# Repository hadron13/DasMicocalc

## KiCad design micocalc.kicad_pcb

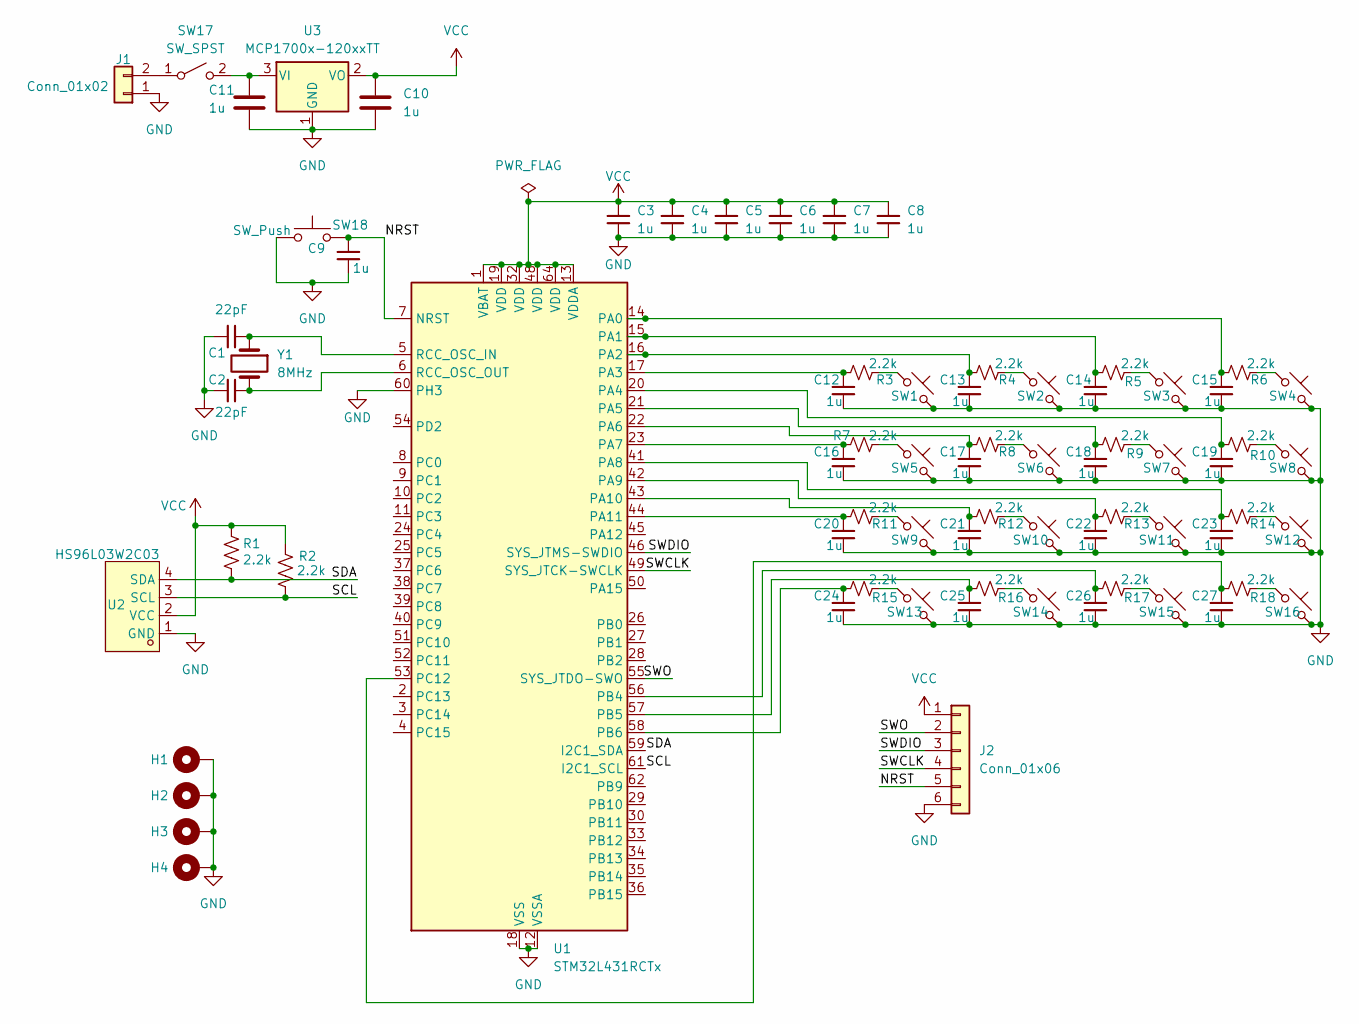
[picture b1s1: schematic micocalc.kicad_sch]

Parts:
C1, C2: 22pF; C_Disc_D3.0mm_W2.0mm_P2.50mm
C3, C4, C5, C6, C7, C8, C9, C10, C11, C12, C13, C14, C15, C16, C17, C18, C19, C20, C21, C22, C23, C24, C25, C26, C27: 1u; C_0603_1608Metric_Pad1.08x0.95mm_HandSolder
H1, H2, H3, H4: MountingHole_Pad; MountingHole_2.2mm_M2_Pad_Via
J1: Conn_01x02; PinHeader_1x02_P2.54mm_Vertical
J2: Conn_01x06; PinSocket_1x06_P2.54mm_Vertical
R1, R2, R3, R4, R5, R6, R7, R8, R9, R10, R11, R12, R13, R14, R15, R16, R17, R18: 2.2k; R_0603_1608Metric_Pad0.98x0.95mm_HandSolder
SW1, SW2, SW3, SW4, SW5, SW6, SW7, SW8, SW9, SW10, SW11, SW12, SW13, SW14, SW15, SW16: SW_Push_45deg; SW_Push_1P1T_NO_E-Switch_TL3301NxxxxxG
SW17: SW_SPST; SW-TH_3P-L8.6-W4.5-P2.60
SW18: SW_Push; SW_Push_1P1T_NO_E-Switch_TL3301NxxxxxG
U1: STM32L431RCTx; LQFP-64_10x10mm_P0.5mm
U2: HS96L03W2C03; OLED-TH_L27.8-W27.2-P2.54_C9900033791; LCSC Part C5248080
U3: MCP1700x-120xxTT; SOT-23
Y1: 8MHz; Crystal_HC49-U_Vertical

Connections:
/NRST: C9.1, J2.5, SW18.2, U1.7 (NRST)
/SCL: R2.2, U1.61 (I2C1_SCL), U2.3 (SCL)
/SDA: R1.2, U1.59 (I2C1_SDA), U2.4 (SDA)
/SWCLK: J2.4, U1.49 (SYS_JTCK-SWCLK)
/SWDIO: J2.3, U1.46 (SYS_JTMS-SWDIO)
/SWO: J2.2, U1.55 (SYS_JTDO-SWO)
GND: C1.1, C2.1, C3.2, C4.2, C5.2, C6.2, C7.2, C8.2, C9.2, C10.2, C11.2, C12.2, C13.2, C14.2, C15.2, C16.2, C17.2, C18.2, C19.2, C20.2, C21.2, C22.2, C23.2, C24.2, C25.2, C26.2, C27.2, H1.1 (1_1), H2.1 (1_1), H3.1 (1_1), H4.1 (1_1), J1.1, J2.6, SW1.2, SW2.2, SW3.2, SW4.2, SW5.2, SW6.2, SW7.2, SW8.2, SW9.2, SW10.2, SW11.2, SW12.2, SW13.2, SW14.2, SW15.2, SW16.2, SW18.1, U1.12 (VSSA), U1.18 (VSS), U1.31 (VSS), U1.47 (VSS), U1.60 (PH3), U1.63 (VSS), U2.1 (GND), U3.1 (GND)
unnamed: J1.2, SW17.1 (A)
unnamed: R3.2, SW1.1
unnamed: R4.2, SW2.1
unnamed: R5.2, SW3.1
unnamed: R6.2, SW4.1
unnamed: R7.2, SW5.1
unnamed: R8.2, SW6.1
unnamed: R9.2, SW7.1
unnamed: R10.2, SW8.1
unnamed: R11.2, SW9.1
unnamed: R12.2, SW10.1
unnamed: R13.2, SW11.1
unnamed: R14.2, SW12.1
unnamed: R15.2, SW13.1
unnamed: R16.2, SW14.1
unnamed: R17.2, SW15.1
unnamed: R18.2, SW16.1
unnamed: C11.1, SW17.2 (B), U3.3 (VI)
unnamed: C15.1, R6.1, U1.14 (PA0)
unnamed: C14.1, R5.1, U1.15 (PA1)
unnamed: C13.1, R4.1, U1.16 (PA2)
unnamed: C12.1, R3.1, U1.17 (PA3)
unnamed: C19.1, R10.1, U1.20 (PA4)
unnamed: C18.1, R9.1, U1.21 (PA5)
unnamed: C17.1, R8.1, U1.22 (PA6)
unnamed: C16.1, R7.1, U1.23 (PA7)
unnamed: C23.1, R14.1, U1.41 (PA8)
unnamed: C22.1, R13.1, U1.42 (PA9)
unnamed: C21.1, R12.1, U1.43 (PA10)
unnamed: C20.1, R11.1, U1.44 (PA11)
unnamed: C26.1, R17.1, U1.56 (PB4)
unnamed: C25.1, R16.1, U1.57 (PB5)
unnamed: C24.1, R15.1, U1.58 (PB6)
unnamed: C27.1, R18.1, U1.53 (PC12)
unnamed: C1.2, U1.5 (RCC_OSC_IN), Y1.1
unnamed: C2.2, U1.6 (RCC_OSC_OUT), Y1.2
VCC: C3.1, C4.1, C5.1, C6.1, C7.1, C8.1, C10.1, J2.1, R1.1, R2.1, U1.1 (VBAT), U1.13 (VDDA), U1.19 (VDD), U1.32 (VDD), U1.48 (VDD), U1.64 (VDD), U2.2 (VCC), U3.2 (VO)

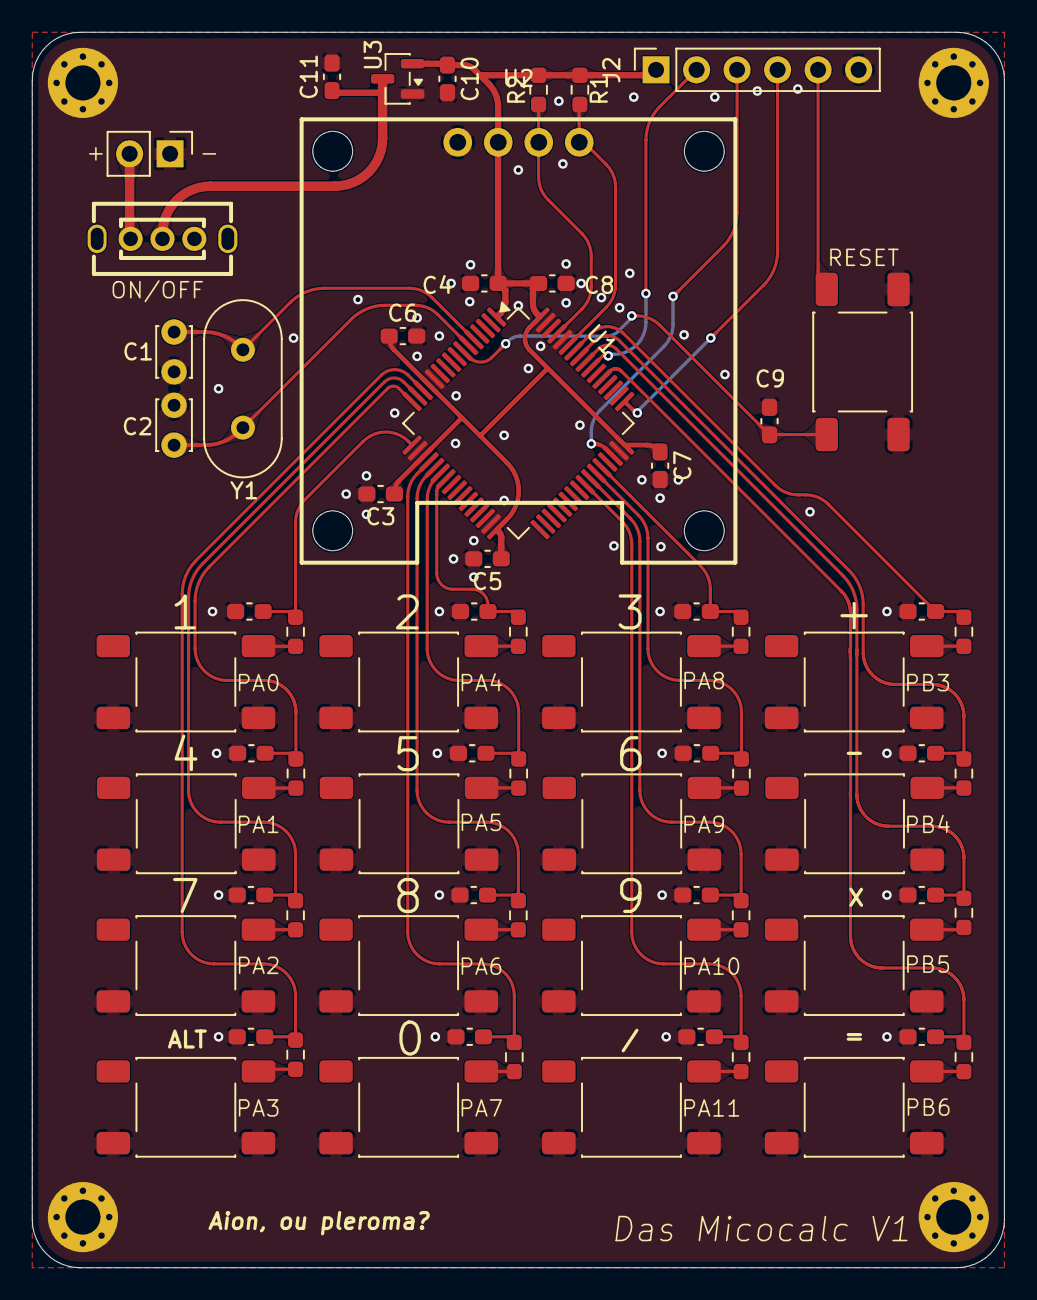
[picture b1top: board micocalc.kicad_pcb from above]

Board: 2 copper layers, 61.0 x 77.5 mm, 73 parts (0 on the bottom side), 44 nets.
